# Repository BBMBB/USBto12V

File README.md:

# USBto12V

Simple 5V DC (USB) to 12V DC boost converter based on the MC34063.

It is designed as a low power device for currents < 100mA.

BOM and Gerber-Files are available.

## Pictures

## Dimensions

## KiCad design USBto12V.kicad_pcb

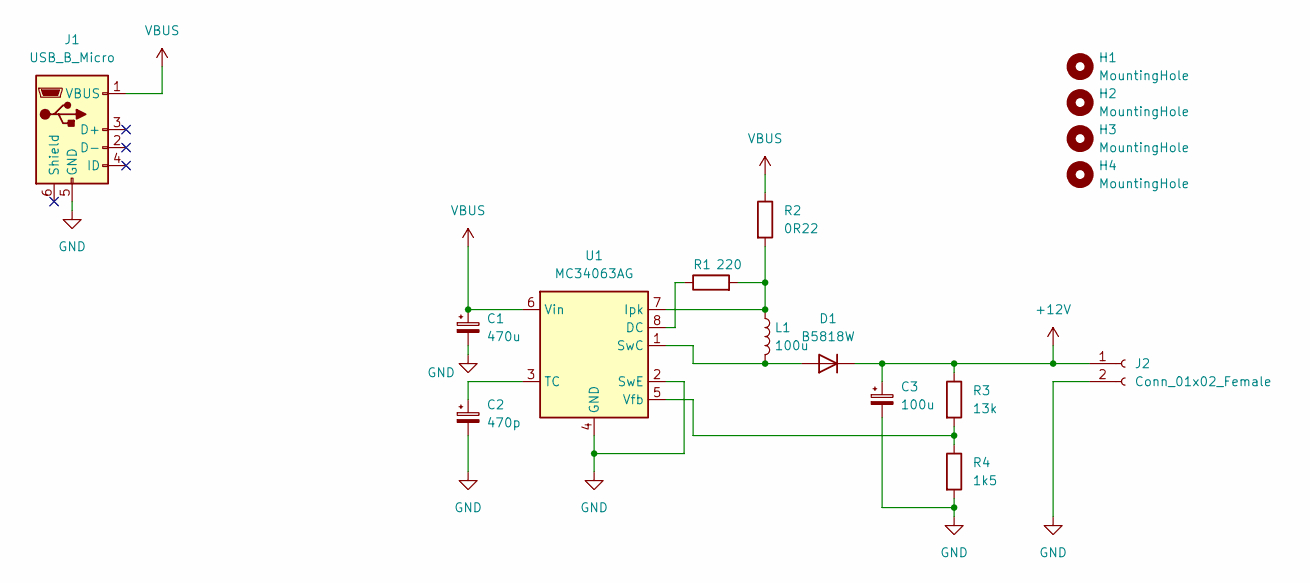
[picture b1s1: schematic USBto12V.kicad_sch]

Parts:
C1: 470u; CP_Elec_8x10.5; LCSC C141429
C2: 470p; C_0603_1608Metric_Pad1.08x0.95mm_HandSolder; LCSC C123573
C3: 100u; CP_Elec_6.3x7.7; LCSC C125975
D1: B5818W; D_SOD-123; LCSC C21571
H1, H2, H3, H4: MountingHole; MountingHole_4.3mm_M4_DIN965
J1: USB_B_Micro; USB_Micro-B_Molex-105017-0001; LCSC C136000
J2: Conn_01x02_Female; TerminalBlock_bornier-2_P5.08mm
L1: 100u; L_1812_4532Metric_Pad1.30x3.40mm_HandSolder; LCSC C76822
R1: 220; R_0603_1608Metric_Pad0.98x0.95mm_HandSolder; LCSC C22962
R2: 0R22; R_0603_1608Metric_Pad0.98x0.95mm_HandSolder; LCSC C20686
R3: 13k; R_0603_1608Metric_Pad0.98x0.95mm_HandSolder; LCSC C286570
R4: 1k5; R_0603_1608Metric_Pad0.98x0.95mm_HandSolder; LCSC C22843
U1: MC34063AG; SOP-8_3.9x4.9mm_P1.27mm; LCSC C71111

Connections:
+12V: C3.1, D1.1 (K), J2.1, R3.1
GND: C1.2, C2.2, C3.2, J1.5 (GND), J2.2, R4.2, U1.2 (SwE), U1.4 (GND)
unnamed: C2.1, U1.3 (TC)
unnamed: D1.2 (A), L1.2, U1.1 (SwC)
unnamed: L1.1, R1.2, R2.2, U1.7 (Ipk)
unnamed: R1.1, U1.8 (DC)
unnamed: R3.2, R4.1, U1.5 (Vfb)
VBUS: C1.1, J1.1 (VBUS), R2.1, U1.6 (Vin)

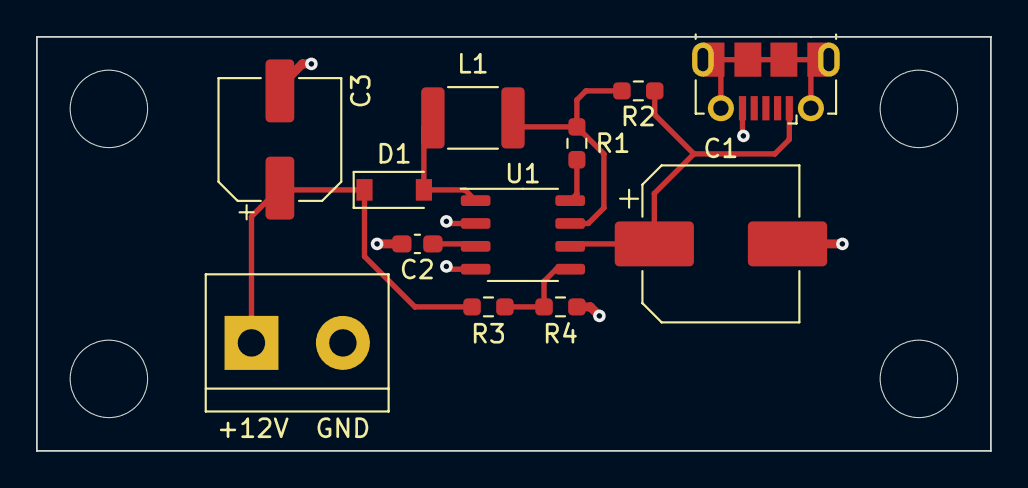
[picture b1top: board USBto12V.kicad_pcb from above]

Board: 2 copper layers, 53.0 x 23.0 mm, 16 parts (0 on the bottom side), 8 nets.

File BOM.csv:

"Item","Qty","Reference(s)","Value","LibPart","Footprint","Datasheet","LCSC"
"1","1","C1","470u","Device:C_Polarized_Small","Capacitor_SMD:CP_Elec_8x10.5","~","C141429"
"2","1","C2","470p","Device:C_Polarized_Small","Capacitor_SMD:C_0603_1608Metric_Pad1.08x0.95mm_HandSolder","~","C123573"
"3","1","C3","100u","Device:C_Polarized_Small","Capacitor_SMD:CP_Elec_6.3x7.7","~","C125975"
"4","1","D1","B5818W","Device:D","Diode_SMD:D_SOD-123","~","C21571"
"5","4","H1, H2, H3, H4","MountingHole","Mechanical:MountingHole","MountingHole:MountingHole_4.3mm_M4_DIN965","~",""
"6","1","J1","USB_B_Micro","Connector:USB_B_Micro","Connector_USB:USB_Micro-B_Molex-105017-0001","https://datasheet.lcsc.com/lcsc/1811131824_MOLEX-1050170001_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","C136000"
"7","1","J2","Conn_01x02_Female","Connector:Conn_01x02_Female","TerminalBlock:TerminalBlock_bornier-2_P5.08mm","~",""
"8","1","L1","100u","Device:L","Inductor_SMD:L_1812_4532Metric_Pad1.30x3.40mm_HandSolder","~","C76822"
"9","1","R1","220","Device:R","Resistor_SMD:R_0603_1608Metric_Pad0.98x0.95mm_HandSolder","~","C22962"
"10","1","R2","0R22","Device:R","Resistor_SMD:R_0603_1608Metric_Pad0.98x0.95mm_HandSolder","~","C20686"
"11","1","R3","13k","Device:R","Resistor_SMD:R_0603_1608Metric_Pad0.98x0.95mm_HandSolder","~","C286570"
"12","1","R4","1k5","Device:R","Resistor_SMD:R_0603_1608Metric_Pad0.98x0.95mm_HandSolder","~","C22843"
"13","1","U1","MC34063AG","Regulator_Switching:MC34063AD","Package_SO:SOP-8_3.9x4.9mm_P1.27mm","https://datasheet.lcsc.com/lcsc/1810252010_UTC-Unisonic-Tech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","C71111"

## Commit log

2022-03-07 First Commit. Added project files
2022-03-07 Added BOM and Gerber files
2022-03-11 Added pictures for the README
2022-03-11 Added Dimensions
2022-03-11 Added README
